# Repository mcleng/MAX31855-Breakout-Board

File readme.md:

MAX31855 Breakout Board
=======================

This work is licensed under a <a rel="license" href="http://creativecommons.org/licenses/by-sa/3.0/">Creative Commons Attribution-ShareAlike 3.0 Unported License</a>.

Designed By:

*	Ryan McLaughlin <ryan@ryanjmclaughlin.com>

Summary
-------

This is a simple low-cost breakout for the MAX31855 thermocouple to digital interface from Maxim.  Rather than using a standard SOIC to DIP adapter, you can use this handy breakout to connect a thermocouple and the recommended cap for the IC is already included.  Comes with SMT soldering complete and headers loose.  Also included is a 4050 level shifter for using the chip with 5V systems.

**CAUTION: The MAX31855 is for 3.3V only! If connecting to a 5V system, you must use a level shifter!!**

Tutorial
--------

It is simple to get everything up and running.

1.	Install a header or solder jumper wires to the pin connections
2.	Connect a K-Type [Thermocouple](http://en.wikipedia.org/wiki/Thermocouple Thermocouple) to the terminals
3.	Wire the necessary connections to an Arduino or other micro controller, the bare minimum connections are +V, GND, SCK, SO, CS  **CAUTION: The MAX31855 is for 3.3V only! If connecting to a 5V system, you must use a level shifter!!**
4.	If using an Arduino, load one of the samples from the MAX31855 Arduino Library and you should see temperature information in the serial console. With other micro controllers you can access the chip using a standard SPI interface. See MAX31855 data sheet for more details.

Board Specs
-----------

*	Dimensions: 0.6" x 0.5"
*	Chip: MAX31855
*	Voltage: 3.3V
*	Header: 1x3 (2) 0.1" Pitch

Versions
--------

###Version 1.1

Primary change with this version was to remove the small SMT header with  more standard 3.5mm screw terminal.

* Updated the layout and routing for the new terminals
* Kept the existing DIP layout
* Overall footprint reduced to 0.6" x 0.5"

####Board Specs

*	Dimensions: 0.6" x 0.5"
*	Chip: MAX31855
*	Header: 1x3 (2) 0.1" Pitch

###Version 1.0

Initial version of the board with a small SMT header. <small>Licensed under OSHW</small>

* 	Initial release under Eagle 6.1 on Github
*	DIP format for easy breadboarding
*	Recommended cap is included on the breakout
*	Production dates: 05-2011

####Board Specs
*	Dimensions: 0.6" x 0.6"
*	Chip: MAX31855
*	Header: 1x3 (2) 0.1" Pitch

Purchase
--------

[store.ryanjmclaughlin.com](http://store.ryanjmclaughlin.com).

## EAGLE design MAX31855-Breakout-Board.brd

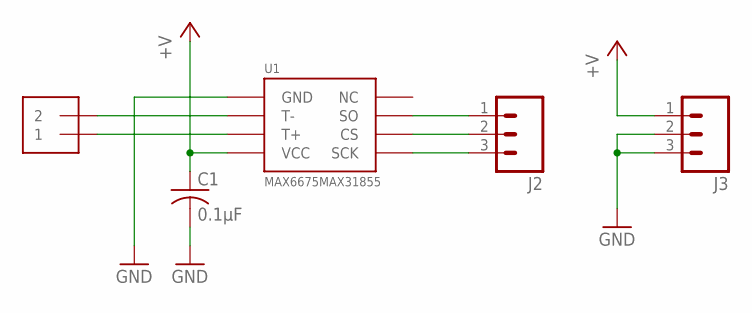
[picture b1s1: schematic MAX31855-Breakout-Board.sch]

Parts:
C1: 0.1µF; C0603
J2, J3: M031X03_NO_SILK; 1X03_NO_SILK
J4: 1X2-3.5MM
U1: MAX6675MAX31855; SOIC-8

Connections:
+5V: C1.1, J3.1, U1.VCC
CS: J2.2, U1.CS
GND: C1.2, J3.2, J3.3, U1.GND
SCK: J2.3, U1.SCK
SO: J2.1, U1.SO
T+: J4.1, U1.T+
T-: J4.2, U1.T-

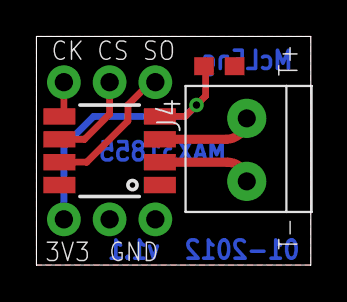
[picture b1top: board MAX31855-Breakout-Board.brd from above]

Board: 2 copper layers, 15.2 x 12.7 mm, 5 parts (0 on the bottom side), 7 nets.

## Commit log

2012-01-30 Initial release on Github, v1.0
2012-01-30 Updated to use screw terminal header and updated for v1.1 and 01-2012 production
2012-01-31 Added schematic and board images/pdf

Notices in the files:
readme.md:
CC BY-SA 3.0
